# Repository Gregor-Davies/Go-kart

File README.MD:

PLEASE SEE THE VERSION 2 BRANCH!

Telemtry (Mainly going to be used in a go-kart) using esp32/LoRA and python (And a bit of c++ & c).

Contributors are welcome!

Python dependencies:
- MatplotLIB (For graphing)
- PySerial (For getting the data off the esp32)
- Tkinter (For the gui controller)
- Datetime (For the timer)
- Numpy
- Serial tools

C/C++ (Arduino) dependencies:                                                                                                                        
**Board Dependencies:**                                                                                                                   
- http://resource.heltec.cn/download/package_heltec_esp32_index.json (Paste this in the additional boards manager in the Arduino IDE.)                           
- Heltec ESP32 (This can be added by searching in the board manager.)  

**Libraries:**                                                                                                                                                                    
- Heltec ESP32 DEV-Boards (This can be found in the library manager.)      

© Gregor Davies, Struan Lawrie & Misha Agakov 2020-2021 Licensed under the MIT License.

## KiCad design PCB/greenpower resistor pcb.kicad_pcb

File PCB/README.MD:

The files to get a pcb made for the temp sensors to work correctly with the esp32

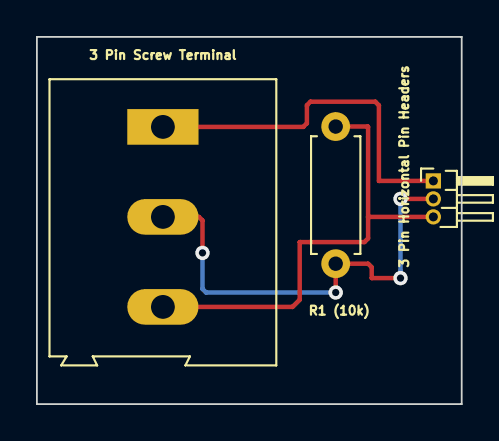
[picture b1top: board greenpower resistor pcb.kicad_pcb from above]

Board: 2 copper layers, 23.6 x 20.4 mm, 3 parts (0 on the bottom side), 3 nets.

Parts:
3 Pin Horizontal Pin Headers: Pin header x 3; PinHeader_1x03_P1.00mm_Horizontal
3 Pin Screw Terminal: Screw_Terminal_01x03; TerminalBlock_Altech_AK300-3_P5.00mm
R1 (10k): 10k; R_Axial_DIN0207_L6.3mm_D2.5mm_P7.62mm_Horizontal

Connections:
unnamed: 3 Pin Horizontal Pin Headers.1, 3 Pin Screw Terminal.1
unnamed: 3 Pin Horizontal Pin Headers.2, 3 Pin Screw Terminal.2, R1 (10k).1
unnamed: 3 Pin Horizontal Pin Headers.3, 3 Pin Screw Terminal.3, R1 (10k).2

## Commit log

2020-10-05 Python Graphing (WIP)
2020-10-05 Arduino
2020-10-05 Sensor Update
2020-10-05 Create LICENSE
2020-10-06 Update LICENSE
2020-10-26 Added Dark background.
2020-10-26 Shorter Links
    Updated the links to a shorter version.
2020-10-27 Tinkter Test GUI
2020-10-27 Renaming the test file.
2020-10-27 Basic GUI Setup
2020-10-29 Added a pitstop button
    It's not currently functional as it requires the hud.
2020-11-03 Rename gui2.py to gui.py
2020-11-10 Early timer.
    Early timer needs to be improved.
2020-11-10 100th Commit!
2020-11-12 Rename test3.py to Graphing_Test.py
2020-11-24 Working on graphing
2020-11-24 Fixed a spelling mistake 👩‍💻
2020-11-24 Updated graphing 📈
2020-11-25 Updated parts lists 📃
2020-11-26 Added information for new sensors 💡
2020-12-01 Rename receiver.ino to receiver_test.ino
2020-12-01 Rename sender.ino to sender_test.ino
2022-06-12 V2 of the software with a web dashboard!
2022-10-30 Speed now displayed on oled
2022-11-01 Now with lora built in
2022-12-13 Added lora reciever test file.
